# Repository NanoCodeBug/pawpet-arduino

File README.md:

# PawPet
Hi! This is the deprecated ardiuno-c++ based codebase, I've moved to a Rust codebase at https://github.com/NanoCodeBug/pawpet. 

# Build Instructions

Arduino SDK, pin layout of board is identical to a Adafruit Feather M0. 

## Linux Arduino SDK and Dependency Setup
tools/linux/sdk-setup.sh

tools/linux/build.sh

## Windows Arduino SDK and Dependency Setup
tools/win/sdk-setup.ps1

tools/win/build.ps1

## Mac Arduino SDK and Dependency Setup
tools/osx/sdk-setup.ps1

tools/osx/build.ps1

# Bootloader Instructions

1. flash adafruit bootloader https://github.com/adafruit/uf2-samdx1
2. set boot brotection fuses to 8kb (bootprot fuse value 0x2)
3. (optional) flash `pawos_setup.hex`
4. disable BOD33 fuse via `pawos_setup.hex` or preffered programmer device

# Flash Instructions

1. connect device via usb
2. double click reset button to enter bootloader
3. flash pawos via arduino-cli (`tools/<plat>/flash.sh`)

# Update Instructions
1. wake PawPet from sleep
2. connect via USB
3. flash pawos via arduino-cli (`tools/<plat>/flash.sh`)

TODO: update instructions that use UF2 instead, should be possible to use a script to put the device into bootloader mode, and then copy the file over via system file browser, or dynamically detect the device attach via usb id and drive name.

TODO: consider a self packaged C# exe or python script?

TODO: look into using openocd for flashing bootloader
TODO: fork adafruit bootloader to have low power operation enabled by default, bootloader blocks startup below 2.2v right now. in theory device can operate to 1.9v before display cuts out

---
# Simulator
A tool to simulate the pawpad on the computer.  
Currently only supports Windows.

## Requirements:

- [Visual Studio Community/MSVC](https://visualstudio.microsoft.com/vs/community/)
- [cmake](https://cmake.org/)
- [SDL2](https://github.com/libsdl-org/SDL/releases)
- [ninja](https://github.com/ninja-build/ninja/releases)
- [emsdk](https://emscripten.org/index.html) (Optional for webSimulator)

### Visual Studio Community
When setting up visual studio community, make sure to select these features:
"Desktop Development with C++"
as we require MSVC  
If you are using VSCode, see the following notes on launching VSCode from the Developer command prompt:  
(https://code.visualstudio.com/docs/cpp/config-msvc#_check-your-microsoft-visual-c-installation)

TODO: Could this possibly be switched to MinCG instead of using MSVC to remove the dependency of Visual Studio Community? [See here](https://code.visualstudio.com/docs/cpp/config-mingw)

### cmake
Install cmake to `C:\Program Files\CMake`

### SDL2
Download `SDL2-devel-[VERSION]-VC.zip` and place SDL2 in `.\simulator\SDL2`

### Ninja
Extract Ninja to `%userprofile%\dev\ninja.exe`

### emsdk
TODO

## Build the simulator
SDL2 and Webasm wrappers.

`tools/win/build.ps1 -simulator`

builds a SDL2 exe version of the pawpet, can be run from `.\build\win32\pawpet.exe`

`tools/win/build.ps1 -webSimulator`

builds a webasm version of the pawpet

## Controls
The Simulator uses the following controls:
```
 - Arrow Keys: dpad operation
 - Z - A Button: Open menu
 - X - B Button
 - C - C Button
 - V - P Button: Select
```

Additional Information in [simulator notes](simulator/notes.md)

---
# Licensing 

## Code
All code is licensed under the MIT license.

## Assets
Graphics, art, and models found in `sprites` and `paw-case` are licensed under the Creative Commons Attribution-NonCommercial 4.0 International Public License.

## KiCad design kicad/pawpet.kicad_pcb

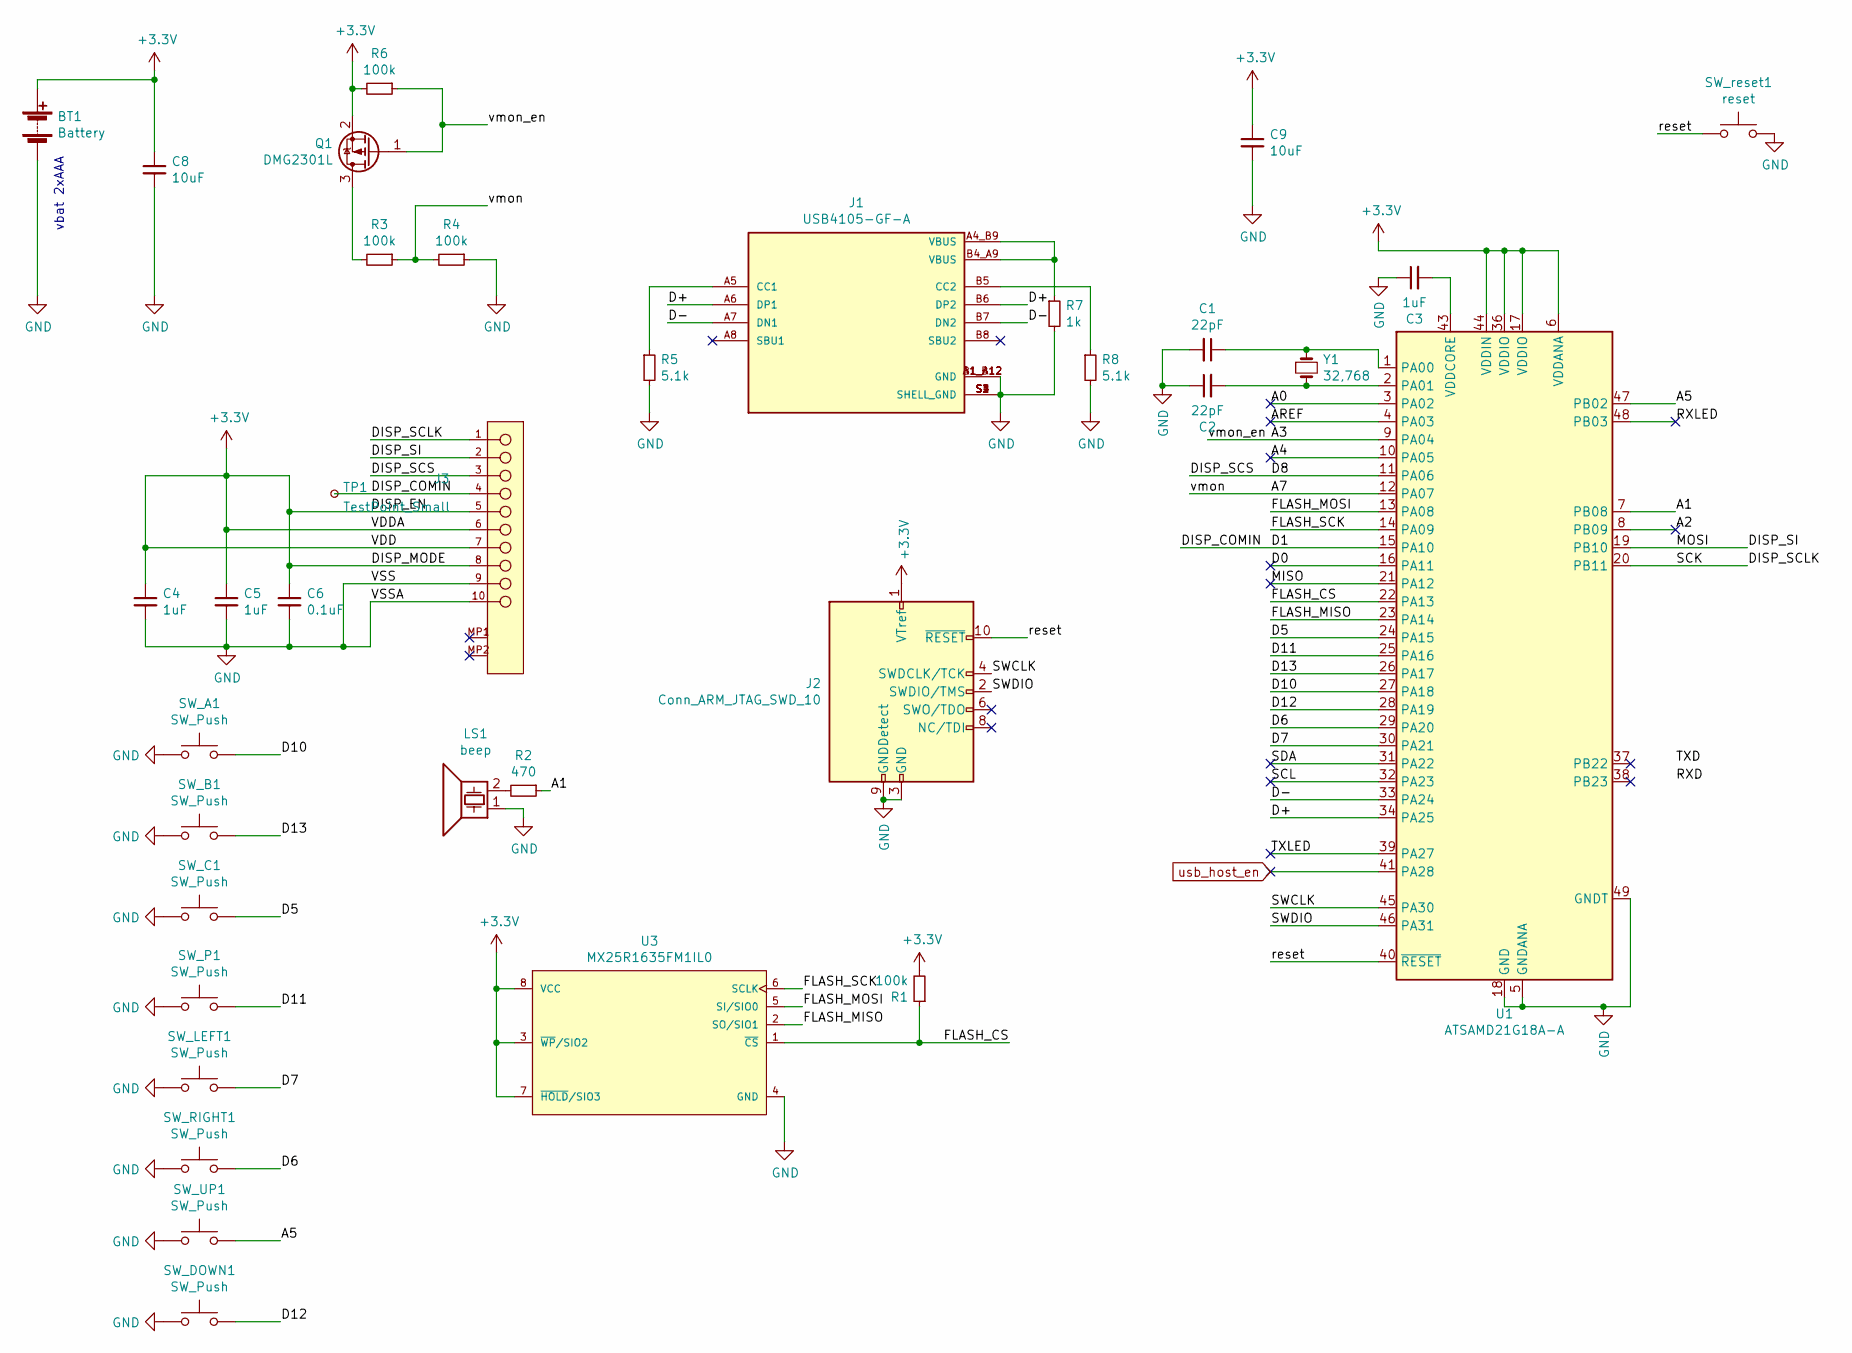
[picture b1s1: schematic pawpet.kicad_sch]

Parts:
BT1: Battery; BAT_BC2AAAPC
C1, C2: 22pF; C_0805_2012Metric
C3, C4, C5: 1uF; C_0805_2012Metric
C6: 0.1uF; C_0805_2012Metric
C8, C9: 10uF; C_0805_2012Metric
J1: USB4105-GF-A; GCT_USB4105-GF-A; PARTREV A3
J2: Conn_ARM_JTAG_SWD_10; Tag-Connect_TC2030-IDC-NL_2x03_P1.27mm_Vertical
J3: MOLEX; Molex-52892-1033-Manufacturer_Recommended
LS1: beep; Buzzer_Murata_PKMCS0909E4000-R1
Q1: DMG2301L; SOT-23
R1, R3, R4, R6: 100k; R_0805_2012Metric
R2: 470; R_0805_2012Metric
R5, R8: 5.1k; R_0805_2012Metric
R7: 1k; R_0805_2012Metric
SW_A1: SW_Push; SW_SPST_EVQQ2
SW_B1: SW_Push; SW_SPST_EVQQ2
SW_C1: SW_Push; SW_SPST_EVQQ2
SW_DOWN1: SW_Push; SW_SPST_EVQQ2
SW_LEFT1: SW_Push; SW_SPST_EVQQ2
SW_P1: SW_Push; SW_SPST_EVQQ2
SW_RIGHT1: SW_Push; SW_SPST_EVQQ2
SW_UP1: SW_Push; SW_SPST_EVQQ2
SW_reset1: reset; SW_SPST_PTS810_handsolder
TP1: TestPoint_Small; TestPoint_Pad_1.0x1.0mm
U1: ATSAMD21G18A-A; TQFP-48-1EP_7x7mm_P0.5mm_EP5x5mm
U3: MX25R1635FM1IL0; SOIC-8_5.23x5.23mm_P1.27mm
Y1: 32,768; Crystal_SMD_2012-2Pin_2.0x1.2mm

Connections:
+3V3: BT1.1 (+), C4.1, C5.1, C6.1, C8.1, C9.1, J2.1 (VTref), J3.5, J3.6, J3.7, J3.8, Q1.2 (S), R1.2, R6.2, U1.6 (VDDANA), U1.17 (VDDIO), U1.36 (VDDIO), U1.44 (VDDIN), U3.3 (~WP/SIO2), U3.7 (~HOLD/SIO3), U3.8 (VCC)
/A0: U1.3 (PA02)
/A1: R2.1, U1.7 (PB08)
/A2: U1.8 (PB09)
/A3: Q1.1 (G), R6.1, U1.9 (PA04)
/A4: U1.10 (PA05)
/A5: SW_UP1.2, U1.47 (PB02)
/A7: R3.1, R4.2, U1.12 (PA07)
/AREF: U1.4 (PA03)
/D0: U1.16 (PA11)
/D1: J3.4, TP1.1, U1.15 (PA10)
/D5: SW_C1.2, U1.24 (PA15)
/D6: SW_RIGHT1.2, U1.29 (PA20)
/D7: SW_LEFT1.2, U1.30 (PA21)
/D8: J3.3, U1.11 (PA06)
/D10: SW_A1.2, U1.27 (PA18)
/D11: SW_P1.2, U1.25 (PA16)
/D12: SW_DOWN1.2, U1.28 (PA19)
/D13: SW_B1.2, U1.26 (PA17)
/D+: J1.A6 (DP1), J1.B6 (DP2), U1.34 (PA25)
/D-: J1.A7 (DN1), J1.B7 (DN2), U1.33 (PA24)
/DISP_SCLK: J3.1, U1.20 (PB11)
/DISP_SI: J3.2, U1.19 (PB10)
/FLASH_CS: R1.1, U1.22 (PA13), U3.1 (~CS)
/FLASH_MISO: U1.23 (PA14), U3.2 (SO/SIO1)
/FLASH_MOSI: U1.13 (PA08), U3.5 (SI/SIO0)
/FLASH_SCK: U1.14 (PA09), U3.6 (SCLK)
/MISO: U1.21 (PA12)
/RXLED: U1.48 (PB03)
/SCL: U1.32 (PA23)
/SDA: U1.31 (PA22)
/SWCLK: J2.4 (SWDCLK/TCK), U1.45 (PA30)
/SWDIO: J2.2 (SWDIO/TMS), U1.46 (PA31)
/TXLED: U1.39 (PA27)
/reset: J2.10 (~RESET), SW_reset1.1, U1.40 (~RESET)
GND: BT1.2 (-), C1.2, C2.1, C3.1, C4.2, C5.2, C6.2, C8.2, C9.2, J1.A1_B12 (GND), J1.B1_A12 (GND), J1.S1 (SHELL_GND), J1.S2 (SHELL_GND), J1.S3 (SHELL_GND), J1.S4 (SHELL_GND), J2.3 (GND), J2.5 (GND), J2.9 (GNDDetect), J3.9, J3.10, LS1.1, R4.1, R5.2, R7.2, R8.2, SW_A1.1, SW_B1.1, SW_C1.1, SW_DOWN1.1, SW_LEFT1.1, SW_P1.1, SW_RIGHT1.1, SW_UP1.1, SW_reset1.2, U1.5 (GNDANA), U1.18 (GND), U1.35 (GND), U1.42 (GND), U1.49 (GNDT), U3.4 (GND)
unnamed: C1.1, U1.1 (PA00), Y1.1
unnamed: C2.2, U1.2 (PA01), Y1.2
unnamed: C3.2, U1.43 (VDDCORE)
unnamed: J1.A4_B9 (VBUS), J1.B4_A9 (VBUS), R7.1
unnamed: J1.A5 (CC1), R5.1
unnamed: J1.B5 (CC2), R8.1
unnamed: LS1.2, R2.2
unnamed: Q1.3 (D), R3.2
usb_host_en: U1.41 (PA28)

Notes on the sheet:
vbat 2xAAA

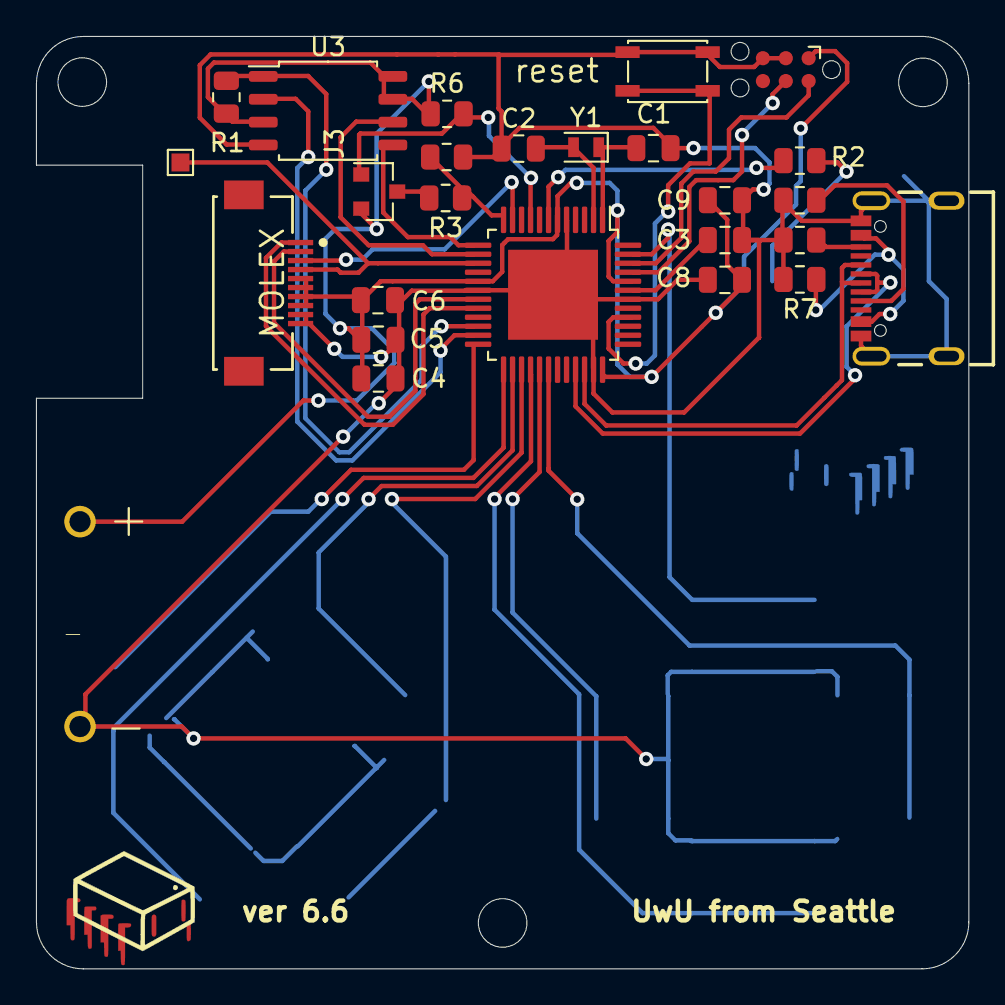
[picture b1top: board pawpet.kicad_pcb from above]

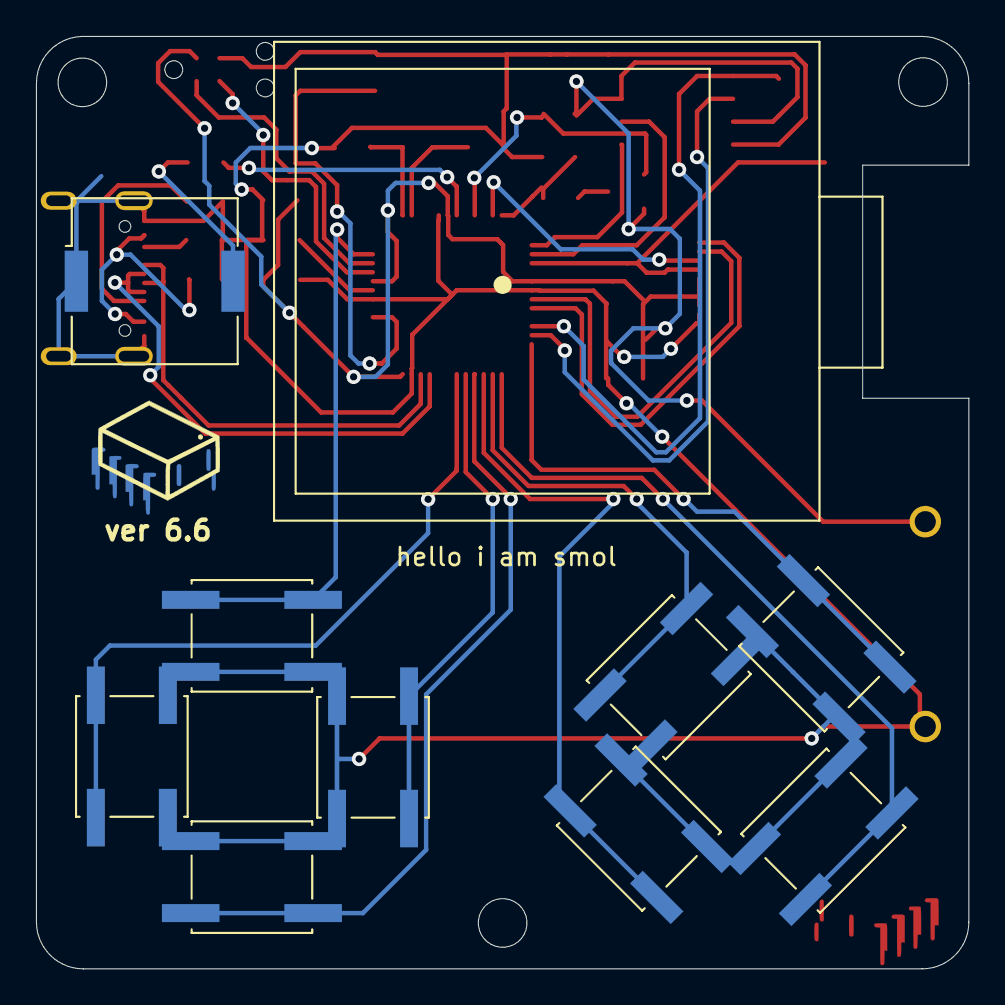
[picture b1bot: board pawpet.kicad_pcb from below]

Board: 2 copper layers, 51.8 x 51.8 mm, 38 parts (11 on the bottom side), 34 nets.

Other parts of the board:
Ref**: Val**; kicad-drawing
Ref**#2: Val**; kicad-drawing
hello i am smol: Sharp_128x128_LS013B7DH03

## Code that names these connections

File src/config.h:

#pragma once

/**
 * pin mappings and chip specific configurations
 * documents unused pins and changes to major board revisions
 */

#define M0_VER_5 1

const unsigned char BUILD_STRING[]{__TIME__[0], __TIME__[1], __TIME__[3], __TIME__[4], __DATE__[0],
                                   __DATE__[1], __DATE__[2], __DATE__[4], __DATE__[5], '\0'};

#define DISP_WIDTH 128
#define DISP_HEIGHT 128

#if defined(M0_VER_5) || defined(M0_VER_6)
// 0 RX
#define DISP_COMIN 1 // PORTA, 10
#define FLASH_MISO 2 // PORTA, 14
#define FLASH_SCK 3  // PORTA, 9
#define FLASH_MOSI 4 // PORTA, 8
#define PIN_BUTTON_C 5
#define PIN_RIGHT 6
#define PIN_LEFT 7
#define SHARP_SS 8
#define PIN_VBAT 9 // A7
#define PIN_BUTTON_A 10
#define PIN_BUTTON_P 11
#define PIN_DOWN 12
#define PIN_BUTTON_B 13
// 14 A0
#define PIN_BEEPER 15 // A1
// 16 A2
#define PIN_VMON_EN 17 // A3
// 18 A4
#define PIN_UP 19     // A5
                      // SDA 20 no pullup?
                      // SCL 21 no pullup?
#define SHARP_MISO 22 // MISO
#define SHARP_MOSI 23 // MOSI
#define SHARP_SCK 24  // SCK
#define FLASH_CS 38   // PORTA, 13

#define RAM_SIZE 32000

#define DISP_ROTATION 1
#endif

// #define MX25R1635F                                                                                                     \
//     {                                                                                                                  \
//         .total_size = (1 << 21), /* 2 MB / 16 Mb */                                                                    \
//             .start_up_time_us = 800, .manufacturer_id = 0xc2, .memory_type = 0x28, .capacity = 0x15,                   \
//         .max_clock_speed_mhz = 33 /*8*/, .quad_enable_bit_mask = 0x40, .has_sector_protection = false,                 \
//         .supports_fast_read = true, .supports_qspi = true, .supports_qspi_writes = true,                               \
//         .write_status_register_split = false, .single_status_byte = true,                                              \
//     }

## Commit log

2021-12-14 init
2021-12-18 power opt tests
2021-12-30 low power tests
2021-12-31 renamed, moved files, added notes on working and non-working features
2022-01-01 added clang format
2022-01-01 cleanup and split files
2022-01-02 working
2022-01-03 new image format
2022-01-19 drawing optimizations
2022-01-23 trying sleepydog and gclk to io
2022-01-25 forked sleepydog to modify clock divisor for longer watchdog timers
2022-01-25 update schematic and stls
2022-01-27 updated to use latest adafruit samd base and gclk output to display vcom
2022-01-27 updated case and flash script
2022-02-01 temp
2022-02-04 map display polarity com to TCC0
2022-02-04 fixed bug in watchdog clock not being mapped, fix broke usb due to cost of doing reset delay
2022-02-04 display working again, refuses to map to glck3 for some reason
2022-02-06 enable standby tcc
2022-02-14 tone test
2022-02-16 update to latest schematic, pcb, and stl files
2022-02-16 fix linux flash script
2022-03-13 setup env for testing and setting fuses
2022-03-14 package test
2022-03-14 test
2022-03-14 remake package
2022-03-14 update crc hash
2022-03-14 rev package
2022-03-14 fix package
2022-03-14 update build scripts and add bootloader binaries
2022-03-15 fix package dependencies, add jlink support
2022-03-15 update sdk setup to only install neccessary cores
2022-03-19 rev package number
2022-03-19 package name
2022-03-19 move files around
2022-03-19 fix size
2022-03-19 fix bossac ver
2022-07-09 add simulator fork
2022-07-09 fix animation var
2022-09-12 build and simulator fixes
2022-09-12 updating to fix linux build compat
2022-09-12 fix package again :)
2022-09-12 i forgor how all of this package stuff works
2023-06-08 Updated Simulator notes
    Updated instructions for building and running the simulator
